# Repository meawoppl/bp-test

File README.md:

# PCB workspace

Choose a board in the portal using the selector configured in [`.kicad-pcb.json`](.kicad-pcb.json).

**Moved out (2026-10-20):**

- The ESP32 + iCE40 "gumstick" module (v1 DF40 module, v2 M.2 draft) and its
  programming carrier now live in **[OrbitalCommons/gumstick](https://github.com/OrbitalCommons/gumstick)**
  (public, history preserved; v1 ordered files under Git tag `v1`). Start with the
  [v1 ICD](https://github.com/OrbitalCommons/gumstick/blob/main/current-df40-connectors/docs/ICD-v1.md).
  It is included here as the submodule `third_party/gumstick`
  (`git submodule update --init`) because the Tesla controller scripts read the carrier.
- The GPS time calibrator, now named **StratumZero** (board, case, firmware,
  gateware, validation plan), lives in **[OrbitalCommons/stratumzero](https://github.com/OrbitalCommons/stratumzero)**
  (private for now).

Boards here:

- [Tesla coil controller](boards/tesla-coil-controller/README.md).
- [Original MainBoard](boards/mainboard-reference): native KiCad import for reference; original Fusion/Eagle exports in [source/fusion](source/fusion).
- Direction LED tester: existing board and fabrication files described below.

# Direction LED Differential Input Test Board

A compact 5 V BNC polarity indicator and Backplane workflow test project.

## Revision C

The schematic, 32 × 20 mm PCB, and fabrication files now match. The board is
73% smaller than the original 75 × 32 mm layout. The BNC body sits at the
left edge with its barrel overhanging, and the two indicators sit together on
the right. All routing is on top copper, with no vias.

- D1 / `+` (green 1206) lights when the BNC center is positive relative to its shell.
- D2 / `-` (red 1206) lights when the center is negative relative to its shell.
- A shared 1 kOhm 0805 resistor feeds directly antiparallel LEDs, limiting current
  and allowing the conducting LED to limit reverse voltage across the other.

There are four components: J1, R1, D1, and D2. R2 is removed.

[Layout drawing](docs/layout-review.svg) · [3D view](docs/layout-3d.png) ·
[Schematic](docs/schematic-review.svg)

## Verification and ordering

KiCad 10.0.6 ERC: **0 violations**. DRC with schematic parity: **0 violations,
0 unconnected items, 0 parity issues**, under the current project settings.
Gerbers, drills, BOM, and placements have been regenerated for revision C.

The package is ready for fabrication/assembly review, not an already approved
order. Confirm JLCPCB stock, through-hole assembly of J1, and LED rotation in
the assembly preview. No physical prototype has been tested. See the
[manufacturing notes](docs/manufacturing-notes.md) and [fabrication package](fab/README.md).

## Project files

| File or directory | Purpose |
| --- | --- |
| `direction-led-tester.kicad_pro` | KiCad project settings |
| `direction-led-tester.kicad_sch` | Revision C schematic |
| `direction-led-tester.kicad_pcb` | Revision C, 32 × 20 mm board |
| `bp-test.kicad_sym` | Vendored KiCad resistor and LED symbols |
| `fp-lib-table`, `sym-lib-table` | Project-local library mappings |
| `Resistor_SMD.pretty/`, `LED_SMD.pretty/` | Local KiCad footprints |
| `3dmodels/` | Resistor and LED STEP models |
| `lcsc/` | BNC symbol, corrected footprint, and STEP/WRL source models |
| `fab/` | Revision C fabrication, assembly, and check outputs |

The [workflow log](docs/plugin-workflow-log.md) records plugin testing and prior
revisions; use the current manufacturing notes for ordering requirements.

## Tesla coil controller

[Acquisition-first controller development](boards/tesla-coil-controller/README.md): eight simultaneous ADC channels, module v1 carrier interface, and two routed UD2.7-derived GDT bridges. This is an unfinished development board, not a fabrication release.

## License

[MIT](LICENSE). Third-party datasheets, vendor 3D models and imported library
files included for reference keep their own terms; see
`NOTICE`.

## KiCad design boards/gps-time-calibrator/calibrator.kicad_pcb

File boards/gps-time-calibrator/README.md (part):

# GPS optical time calibrator carrier — revision A, routed prototype

180 × 100 mm carrier for the **ordered module v1**, using the programming carrier's exact mating contacts and pad numbering. The ordered daughterboard and programmer files are unchanged. Connector-first routing is complete with clean native ERC, DRC and schematic parity. See `docs/routing-review.md` and `fab/STATUS.md` for validation scope and prototype bring-up checks.

## Optical display

Four identical rows of sixteen green 1206 LEDs (YLED1206G / C30584801) show bit 15 at the left through bit 0 at the right. Rows update together, without multiplexing. Each LED has its own **470 Ω, 1%, 0805** resistor. Sixteen AO3400A MOSFETs switch the columns through two SN74LVC541 buffers, with individual gate resistors and pulldowns. Every LED has its own 100 nF bypass beside its resistor (64 identical placements, so all LEDs see the same local supply at turn-on), and each column adds a 10 µF reservoir. All discrete resistors, capacitors and inductors are 0805 or larger; exact substitutions are in `docs/passive-parts-0805.json`.

Expected display current is approximately 0.26–0.33 A with all LEDs on, depending on LED forward voltage. Equal resistors reduce electrical mismatch but do not remove optical bin variation; use a common LED lot and measure brightness, supply bounce and optical edge timing on assembled hardware.

## USB power and installation

J3 is USB-C power and native USB data. The daughterboard and local logic are always powered from VBUS. The ESP32 reads HUSB238 source/contract status over I²C, enables the TPS259531 switched 5 V domain, and independently controls GPS and OCXO regulator enables. The NOR gate is removed. HUSB238 defaults to a 5 V / 3 A request; higher-voltage requests are forbidden because the always-on domain is fed directly from VBUS.

The eFuse has a nominal 2.48 A switched-load limit and approximately 12 ms ramp. Its current mirror is filtered to ESP GPIO3 / ADC1_CH2. Always-on current bypasses this measurement. Firmware must enforce the source's total budget, sequence the rails, and prevent UART back-powering; this firmware is not implemented here. See [power control, pin mapping and thermal calculations](docs/power-control.md).

There are no BOOT/RUN or RESET switches: the installed module stays in normal run mode using its own strap and EN pullups. Its existing firmware/ROM USB behavior must support the intended recovery procedure; this carrier does not provide a hardware boot override.

The module body extends from x=145 to 165 mm and y=10 to 55 mm, flush with the carrier's top edge. J1/J2 are at (155,24.3) and (155,49.3) mm, retaining 25 mm spacing. H1 is at their midpoint (155,36.8). Retain the programmer's 2.0 mm mounting spacer and frozen connector numbering.

## Right-edge connectors and GNSS

Top to bottom: USB-C J3, input SMA J6, output SMA J7, GPS antenna SMA J5. The SMA connectors are Amphenol 132289 edge-launch parts with approximately 11.43 mm projection beyond the edge and a nominal 1.57 mm (.062-inch) board slot.

Input accepts 0–5 V logic into a TLV3501 comparator referenced to half the 5 V supply, nominally 2.5 V. A 3.3 V Schmitt buffer feeds FPGA, ESP32 and GNSS EXTINT. Output is an AHCT buffer producing 5 V logic into a **high-impedance receiver**, not 5 V into a 50 Ω termination. Neither port should be treated as a protected industrial-voltage input.

MAX-M10S provides UART to ESP GPIO43/44 and PPS to FPGA G0 / ESP GPIO38. Its RF pin 11 connects straight along the top layer to J5, following the original board's topology. The receiver was moved left to accommodate the larger 0805 bias choke and capacitor. The module's VCC_RF output feeds the antenna through 10 Ω and 27 nH; confirm antenna current (50 mA maximum), voltage drop and RF performance. The separate antenna power switch is removed. RESET_N connects to ESP32 GPIO40 through 33 Ω. Backup power follows the receiver supply; there is no battery.

## Precision oscillator

Y1 is the manually assembled **Abracon AOC97FAJC-10.0000**, 10 MHz, 3.3 V OCXO. It has a dedicated TPS7A4533 1.5 A linear supply, enabled by GPIO5, local bypassing, and a 33 Ω series clock resistor to J2 pin 32 / FPGA IOB_3B_G6. Allow the specified warmup before precision measurements. This is a concrete replacement for the original project's unpopulated, untested oscillator provision; firmware must be adapted to 10 MHz.

Y1 is separately procured and excluded from the JLCPCB placement/BOM pair. Its local 3D model is an illustrative dimensional envelope, not manufacturer CAD.

## Stackup and release checks

Nominal 1.6 mm, four-layer JLC04161H-7628 construction is intended for the SMA slots. Outer copper 0.035 mm; outer dielectric 0.21040 mm; inner copper 0.0152 mm; core dielectric 1.065 mm. Source: https://jlcpcb.com/impedance . The nominal RF feed remains 0.26 mm wide with a 0.15 mm coplanar-ground clearance target. The manufacturer coated-coplanar calculation gives 50.50 ohm nominal; see `docs/rf/GPS-FEED.md`. Confirm the finished stackup, launch and bias tee at fabrication/bring-up. USB data is routed as a nearby pair for the module's full-speed interface.

The intended optical word is in 1/65536-second units (15.258789 µs per LSB). Sub-LSB calibration uses rolling-shutter transitions; the hardware alone does not establish absolute microsecond accuracy. Existing firmware is incomplete. `docs/display-map.json` and `docs/circuit.json` define the current mapping and circuit.

Canonical KiCad files are authoritative. Initial construction scripts are destructive and must not be rerun over incremental layout work. Generated fabrication and assembly outputs correspond to the routed PCB. Assembly orientation approval, power/thermal measurements and RF/optical timing validation remain prototype release checks.

## Schematic presentation

The complete circuit is on one A1 sheet, with dashed functional sections matching the module schematic. Filters, regulator support parts, bias networks and decouplers are connected by wires and conventional supply/ground symbols. The optical display is grouped into four banks of four columns, each showing its four individual resistor/LED branches, MOSFET and bypass pair. The single-page PDF is `docs/calibrator-schematic.pdf`. Regenerate with `tools/hardware/calibrator_schematic.py`; the generator preserves the audited circuit contract and changes PCB schematic paths only.

### Trigger input filter

C75 is 1 nF C0G, 50 V, 2%, 0805 (CCTC TCC0805COG102G500BT,
JLCPCB C5375915), shunting TRIGGER_LIMIT to GND after R8 (1 kohm).
It sits beside U9 IN+, with its ground pad thermally connected to the ground pour.
With R9 = 100 kohm, ideal low-impedance 0–5 V drive and a 2.5 V threshold,
tau is 0.990 us, cutoff is about 161 kHz, and nominal rising/falling threshold
latencies are 0.696/0.676 us (before comparator/translator delay).
These are calculated RC delays, not measured calibration constants. Source impedance,
amplitude, edge slew and component tolerances change them; short pulses can be rejected.
Account for the complete input path when validating absolute trigger timing.

### Date/time OLED

[Display assembly instructions (PDF)](docs/display-mounting.pdf) · [Editable instructions](docs/display-mounting.md)

DS1 is the HS HS96L03W2C03 (LCSC C5248080), a white 0.96-inch 128x64
SSD1315 I2C OLED module. It is manually installed below the daughterboard/OCXO,
with its four-pin edge toward the top of the carrier. Pin order is GND, 3.3V,
SCL, SDA; the default 7-bit I2C address is 0x3C. ESP_GPIO2 (J1.14) is SCL and
ESP_GPIO1 (J1.13) is SDA. These module pins were previously unused on this carrier.
R174/R175 are 4.7k pull-ups to +3V3_LOGIC. C76/C77 provide 100nF/10uF locally.
All support passives are 0805. Do not supply this module or its bus with 5V.

The footprint uses the manufacturer's 27.30 x 27.80 mm outline, a centered
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
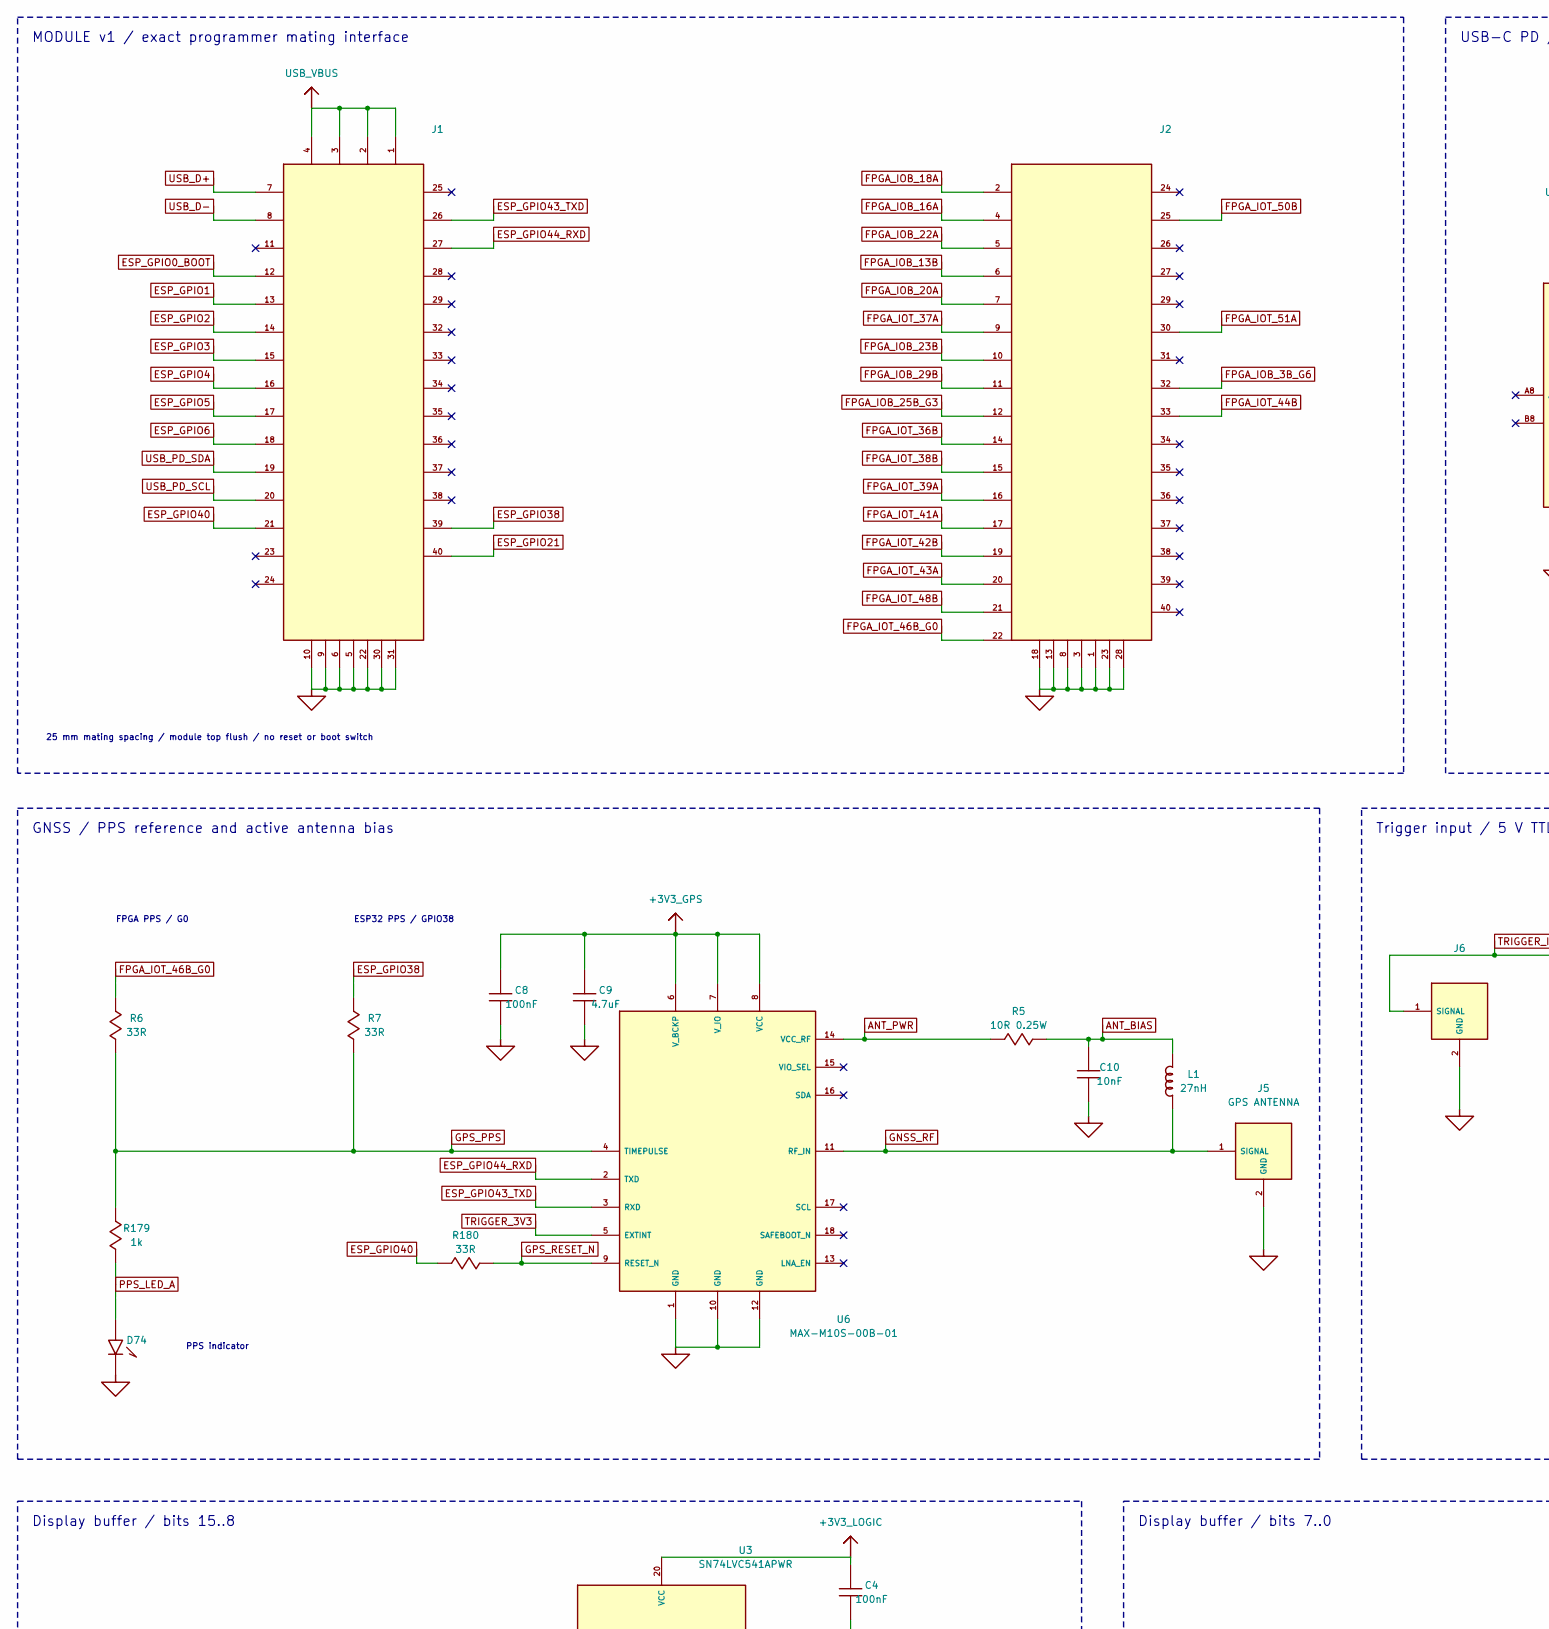
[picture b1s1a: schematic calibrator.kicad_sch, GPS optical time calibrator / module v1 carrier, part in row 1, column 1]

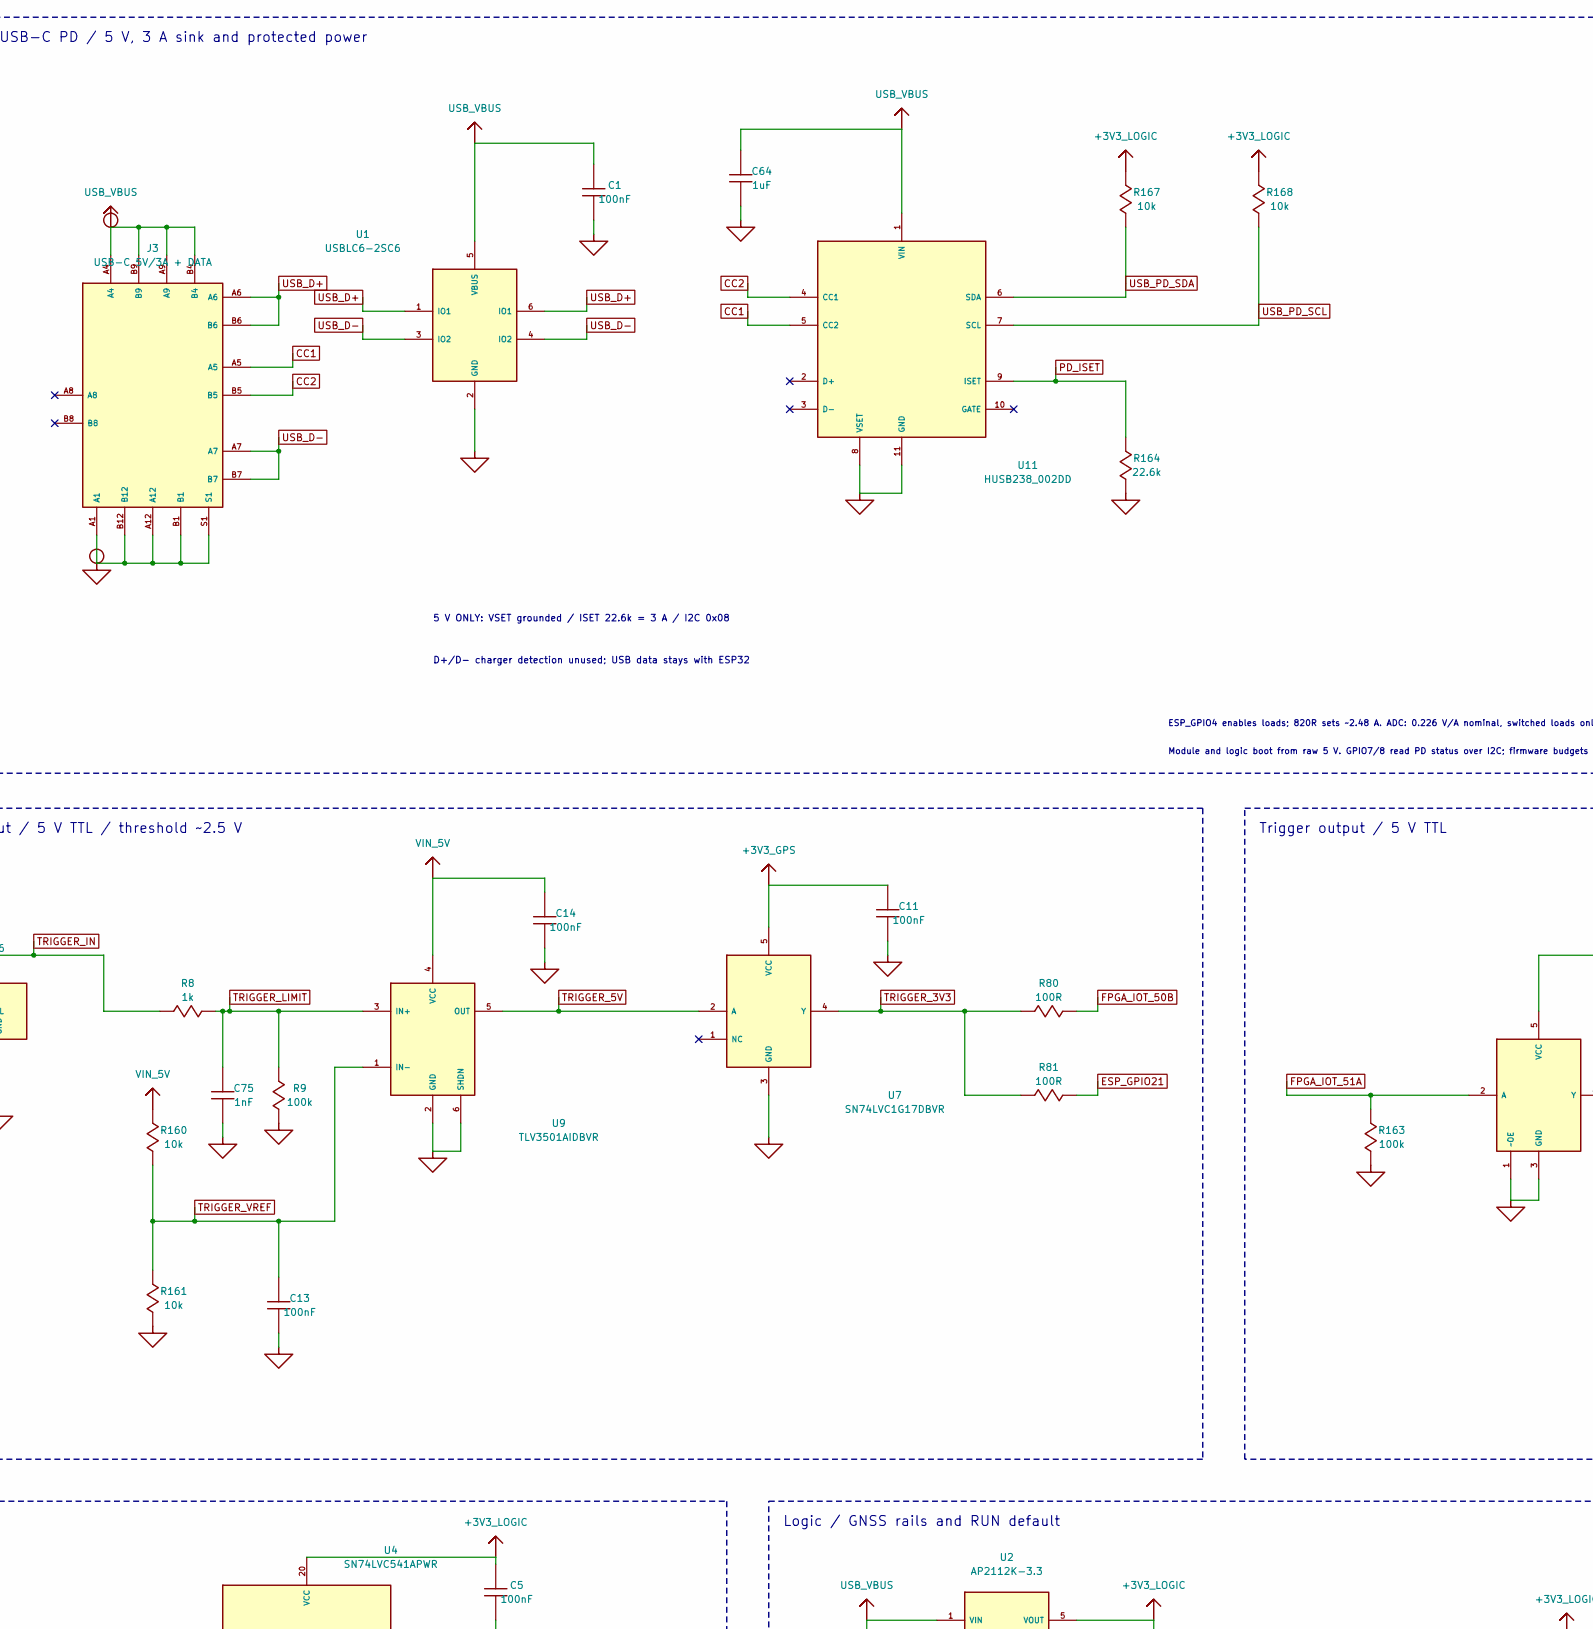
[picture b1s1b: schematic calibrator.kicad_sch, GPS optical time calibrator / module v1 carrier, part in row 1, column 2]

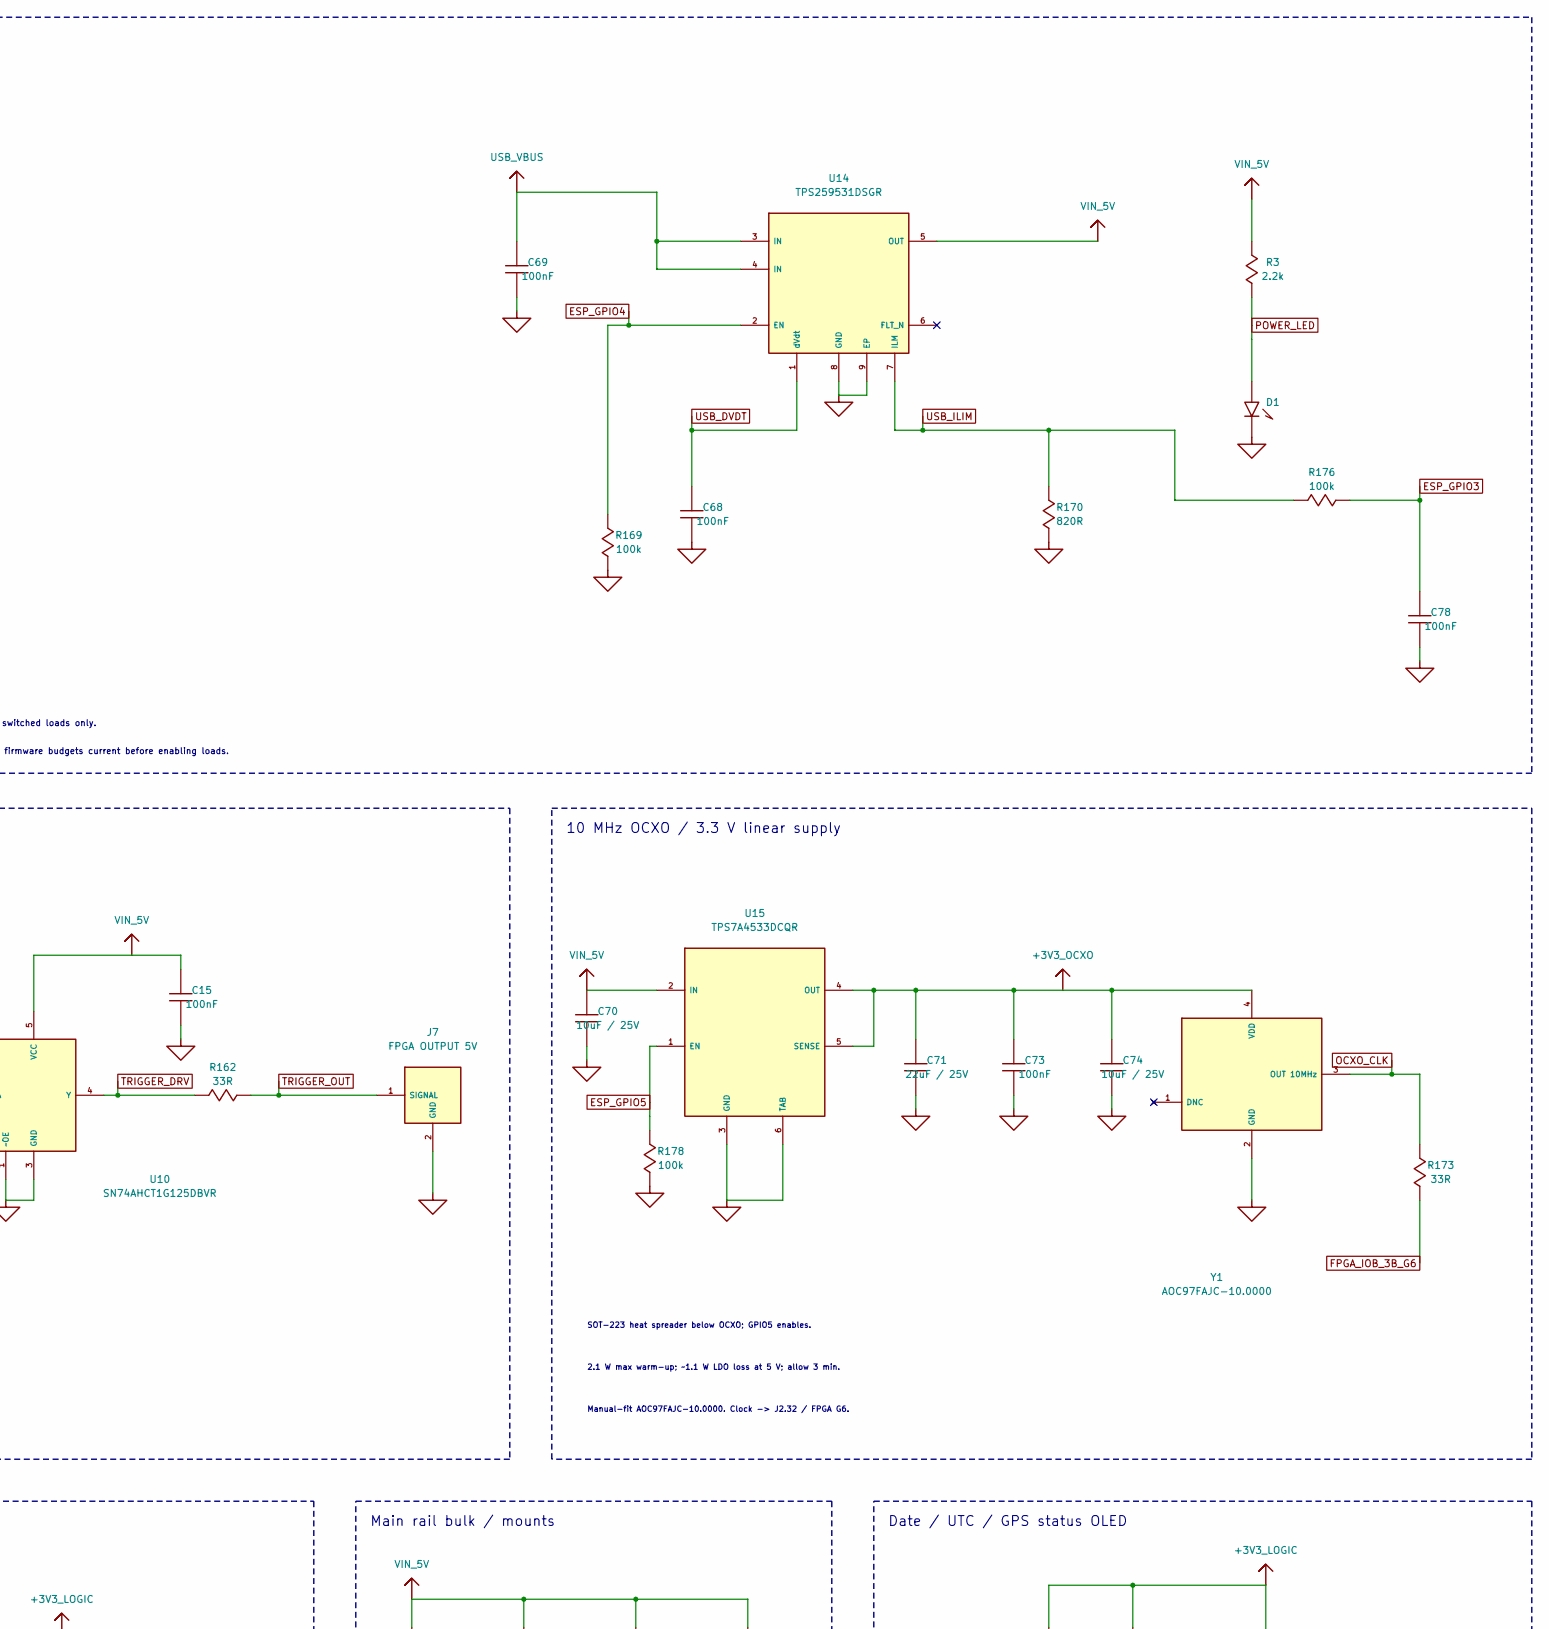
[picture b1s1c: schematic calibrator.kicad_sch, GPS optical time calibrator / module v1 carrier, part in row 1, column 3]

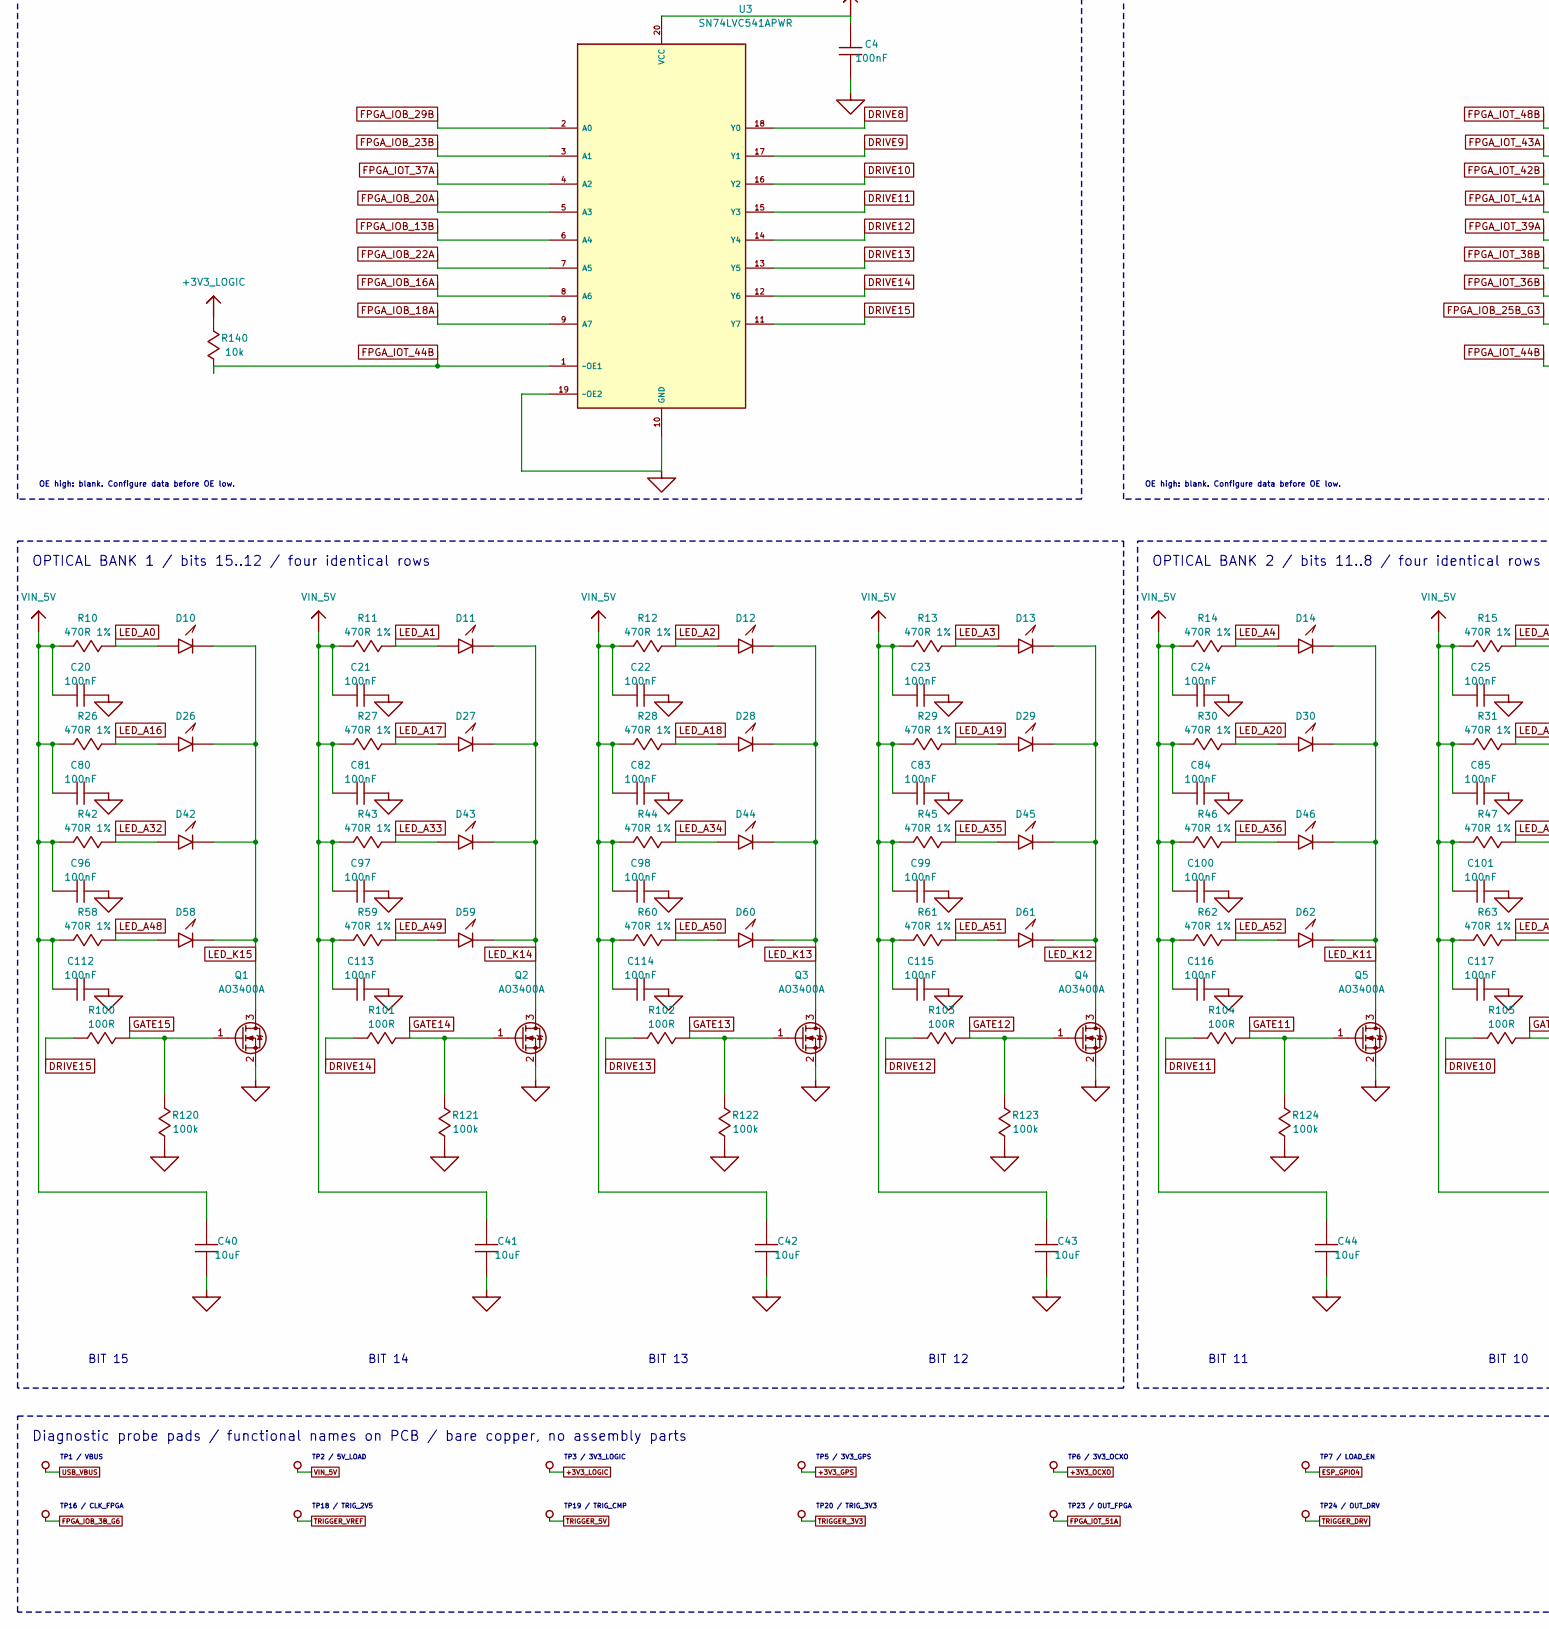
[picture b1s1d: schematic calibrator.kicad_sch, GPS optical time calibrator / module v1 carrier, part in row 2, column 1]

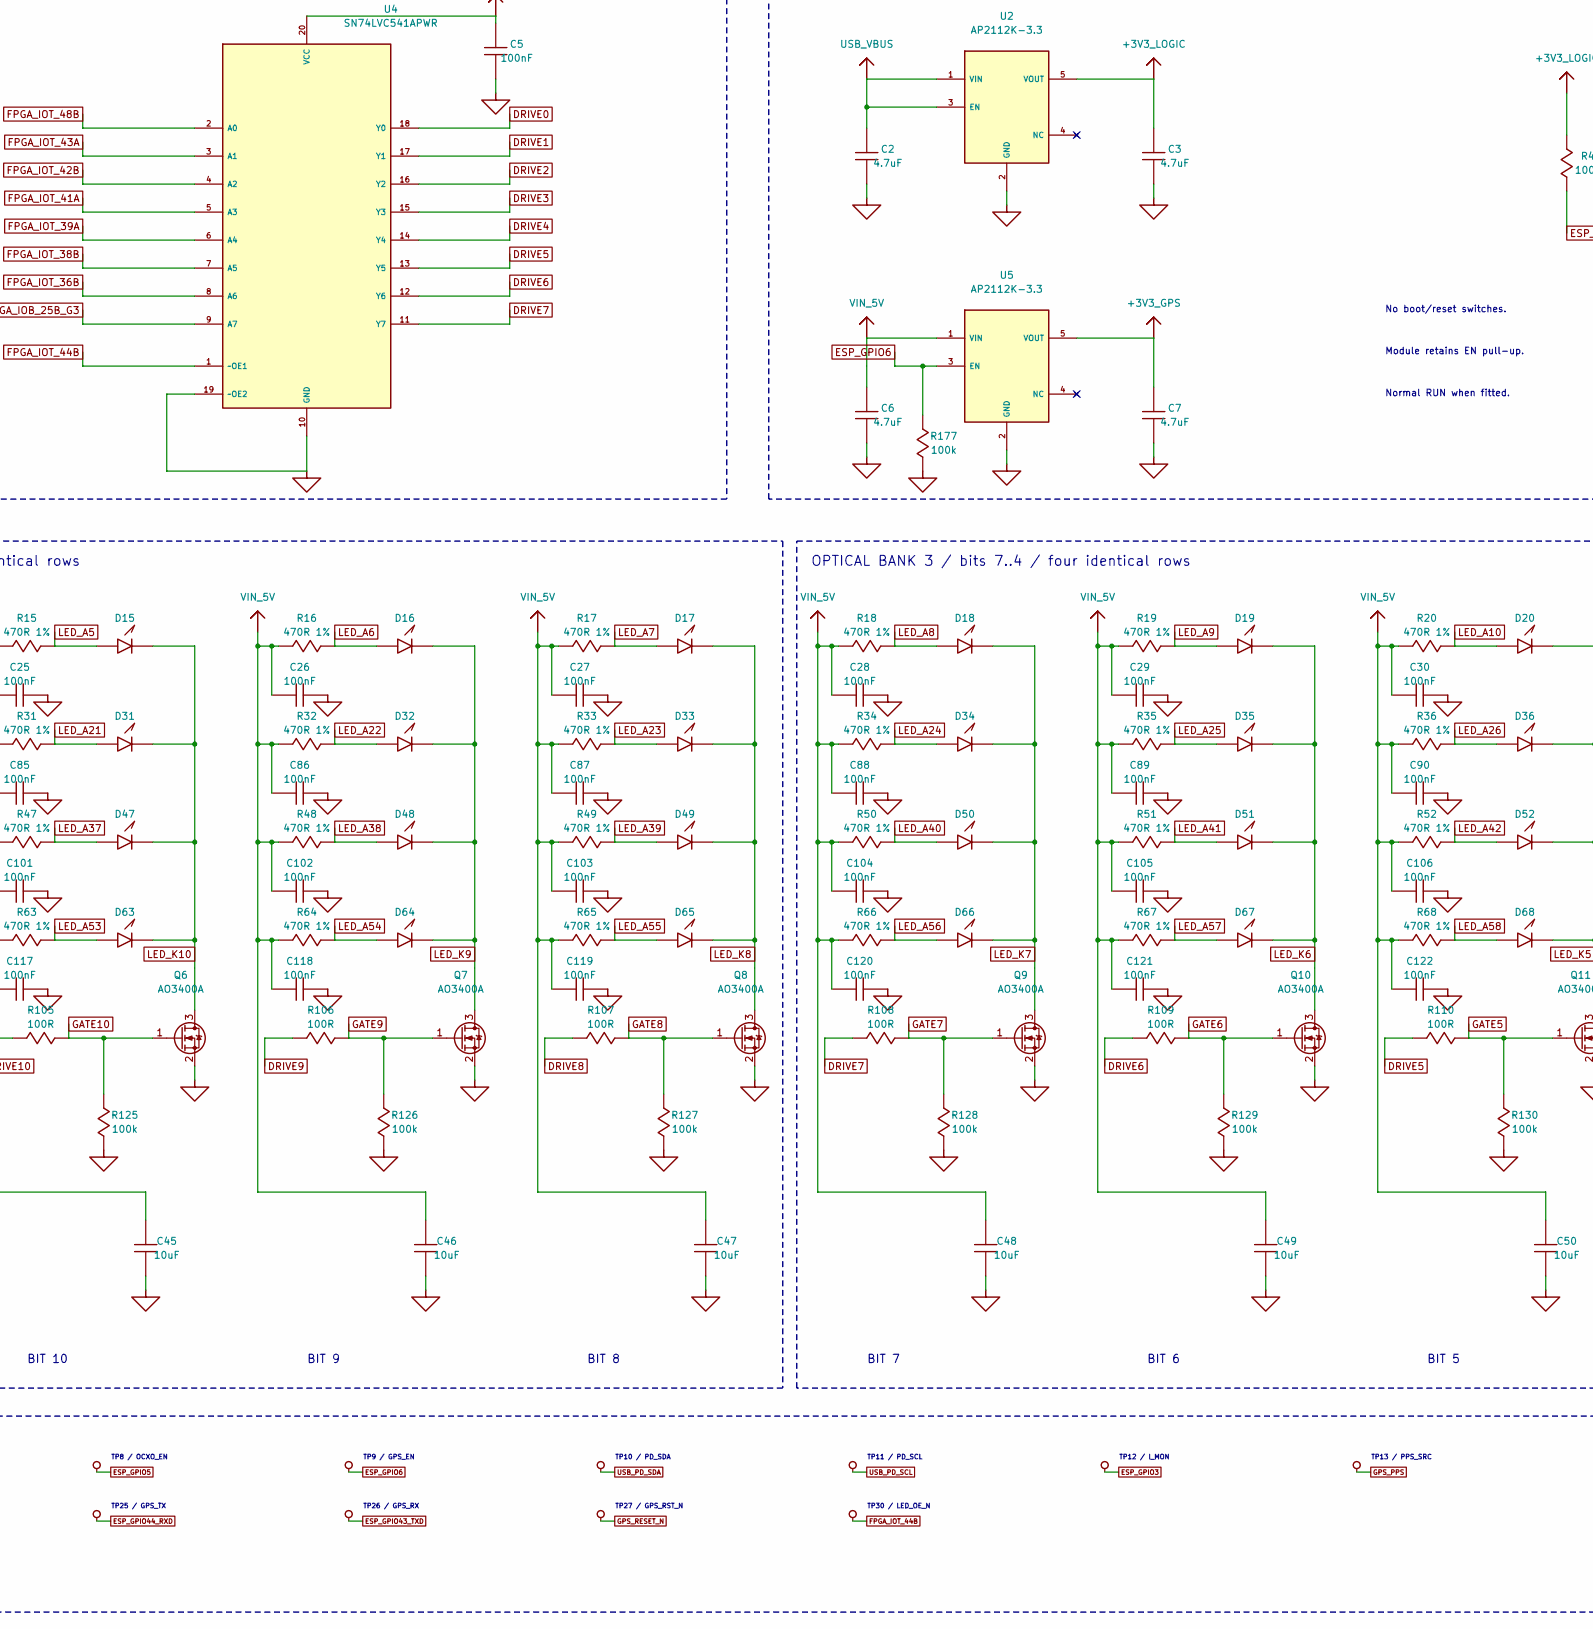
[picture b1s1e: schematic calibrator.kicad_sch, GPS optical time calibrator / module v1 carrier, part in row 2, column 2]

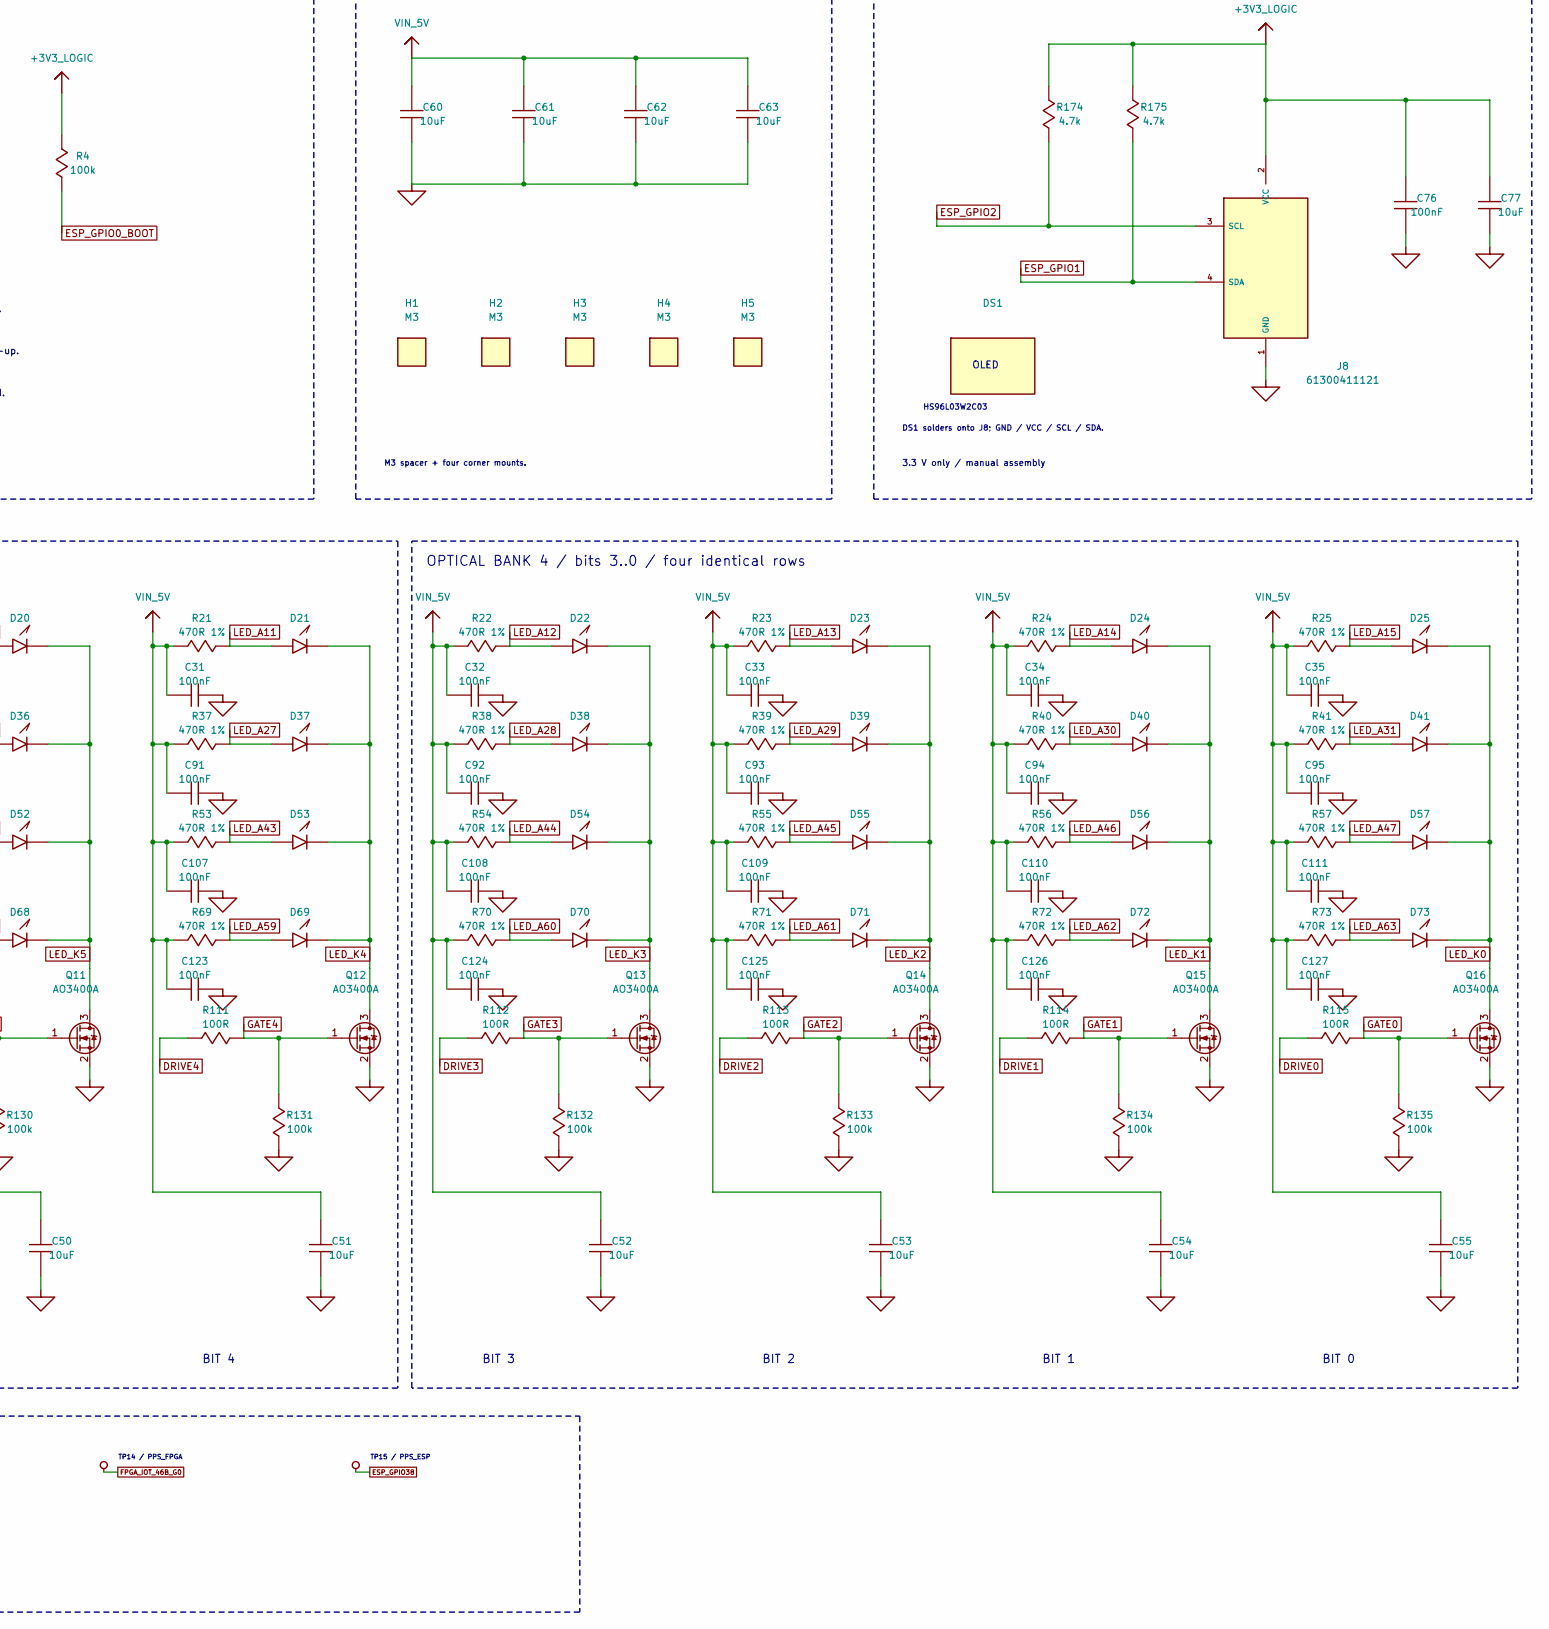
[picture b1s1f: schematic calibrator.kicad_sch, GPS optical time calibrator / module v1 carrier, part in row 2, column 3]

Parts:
C1, C4, C5, C8, C11, C13, C14, C15, C20, C21, C22, C23, C24, C25, C26, C27, C28, C29, C30, C31, C32, C33, C34, C35, C68, C69, C73, C76, C78, C80, C81, C82, C83, C84, C85, C86, C87, C88, C89, C90, C91, C92, C93, C94, C95, C96, C97, C98, C99, C100, C101, C102, C103, C104, C105, C106, C107, C108, C109, C110, C111, C112, C113, C114, C115, C116, C117, C118, C119, C120, C121, C122, C123, C124, C125, C126, C127: 100nF; C_0805_2012Metric; MPN CL21B104KBCNNNC; LCSC C1711
C2, C3, C6, C7, C9: 4.7uF; C_0805_2012Metric; MPN CL21A475KAQNNNE; LCSC C1779
C10: 10nF; C_0805_2012Metric; MPN CL21B103KBANNNC; LCSC C1710
C40, C41, C42, C43, C44, C45, C46, C47, C48, C49, C50, C51, C52, C53, C54, C55, C60, C61, C62, C63, C77: 10uF; C_0805_2012Metric; MPN CL21A106KAYNNNE; LCSC C15850
C64: 1uF; C_0805_2012Metric; MPN CL21B105KBFNNNE; LCSC C28323
C70, C74: 10uF / 25V; C_0805_2012Metric; MPN CL21A106KAYNNNE; LCSC C15850
C71: 22uF / 25V; C_0805_2012Metric; MPN CL21A226MAQNNNE; LCSC C45783
C75: 1nF; C_0805_2012Metric; MPN 0805CG102J500NT; LCSC C29925
D1, D74: GREEN; LED_0603_1608Metric; MPN XL-1608SYGC-06; LCSC C965805
D10, D11, D12, D13, D14, D15, D16, D17, D18, D19, D20, D21, D22, D23, D24, D25, D26, D27, D28, D29, D30, D31, D32, D33, D34, D35, D36, D37, D38, D39, D40, D41, D42, D43, D44, D45, D46, D47, D48, D49, D50, D51, D52, D53, D54, D55, D56, D57, D58, D59, D60, D61, D62, D63, D64, D65, D66, D67, D68, D69, D70, D71, D72, D73: GREEN; LED_1206_3216Metric; MPN YLED1206G; LCSC C30584801
DS1: HS96L03W2C03; HS96L03W2C03_27.3x27.8mm; MPN HS96L03W2C03; LCSC C5248080
H1, H2, H3, H4, H5: M3; MountingHole_3.2mm_M3; MPN M3
J1: DF40C-40DP-0.4V(51); J1_Module_v1_Mate; MPN DF40C-40DP-0.4V(51); LCSC C424643
J2: DF40C(2.0)-40DS-0.4V(51); J2_Module_v1_Mate; MPN DF40C(2.0)-40DS-0.4V(51); LCSC C597934
J3: USB-C 5V/3A + DATA; USB_C_Receptacle_HRO_TYPE-C-31-M-12; MPN TYPE-C-31-M-12; LCSC C165948
J5: GPS ANTENNA; SMA_Amphenol_132289_EdgeMount; MPN 132289; LCSC C3172723
J6: INPUT 5V / 2.5V THRESHOLD; SMA_Amphenol_132289_EdgeMount; MPN 132289; LCSC C3172723
J7: FPGA OUTPUT 5V; SMA_Amphenol_132289_EdgeMount; MPN 132289; LCSC C3172723
J8: 61300411121; OLED_Header_1x04_P2.54mm; MPN 61300411121; LCSC C5184785
L1: 27nH; L_Coilcraft_0805CS; MPN 0805CS-270XGLC; LCSC C38841159
Q1, Q2, Q3, Q4, Q5, Q6, Q7, Q8, Q9, Q10, Q11, Q12, Q13, Q14, Q15, Q16: AO3400A; SOT-23; MPN AO3400A; LCSC C20917
R3: 2.2k; R_0805_2012Metric; MPN 0805W8F2201T5E; LCSC C17520
R4, R9, R120, R121, R122, R123, R124, R125, R126, R127, R128, R129, R130, R131, R132, R133, R134, R135, R163, R169, R176, R177, R178: 100k; R_0805_2012Metric; MPN RC0805FR-07100KL; LCSC C96346
R5: 10R 0.25W; R_1206_3216Metric; MPN 1206W4F100JT5E; LCSC C17903
R6, R7, R162, R173, R180: 33R; R_0805_2012Metric; MPN 0805W8F330JT5E; LCSC C17634
R8, R179: 1k; R_0805_2012Metric; MPN 0805W8F1001T5E; LCSC C17513
R10, R11, R12, R13, R14, R15, R16, R17, R18, R19, R20, R21, R22, R23, R24, R25, R26, R27, R28, R29, R30, R31, R32, R33, R34, R35, R36, R37, R38, R39, R40, R41, R42, R43, R44, R45, R46, R47, R48, R49, R50, R51, R52, R53, R54, R55, R56, R57, R58, R59, R60, R61, R62, R63, R64, R65, R66, R67, R68, R69, R70, R71, R72, R73: 470R 1%; R_0805_2012Metric; MPN 0805W8F4700T5E; LCSC C17710
R80, R81, R100, R101, R102, R103, R104, R105, R106, R107, R108, R109, R110, R111, R112, R113, R114, R115: 100R; R_0805_2012Metric; MPN RC0805FR-07100RL; LCSC C105577
R140, R160, R161, R167, R168: 10k; R_0805_2012Metric; MPN 0805W8F1002T5E; LCSC C17414
R164: 22.6k; R_0805_2012Metric; MPN SCR0805F22K6; LCSC C3016901
R170: 820R; R_0805_2012Metric; MPN 0805W8F8200T5E; LCSC C17837
R174, R175: 4.7k; R_0805_2012Metric; MPN 0805W8F4701T5E; LCSC C17673
TP1: VBUS; TP_1p0mm
TP2: 5V_LOAD; TP_1p0mm
TP3: 3V3_LOGIC; TP_1p0mm
TP5: 3V3_GPS; TP_1p0mm
TP6: 3V3_OCXO; TP_1p0mm
TP7: LOAD_EN; TP_1p0mm
TP8: OCXO_EN; TP_1p0mm
TP9: GPS_EN; TP_1p0mm
TP10: PD_SDA; TP_1p0mm
TP11: PD_SCL; TP_1p0mm
TP12: I_MON; TP_1p0mm
TP13: PPS_SRC; TP_1p0mm
TP14: PPS_FPGA; TP_1p0mm
TP15: PPS_ESP; TP_1p0mm
TP16: CLK_FPGA; TP_1p0mm
TP18: TRIG_2V5; TP_1p0mm
TP19: TRIG_CMP; TP_1p0mm
TP20: TRIG_3V3; TP_1p0mm
TP23: OUT_FPGA; TP_1p0mm
TP24: OUT_DRV; TP_1p0mm
TP25: GPS_TX; TP_1p0mm
TP26: GPS_RX; TP_1p0mm
TP27: GPS_RST_N; TP_1p0mm
TP30: LED_OE_N; TP_1p0mm
U1: USBLC6-2SC6; SOT-23-6_U1; MPN USBLC6-2SC6; LCSC C7519
U2, U5: AP2112K-3.3; SOT-23-5; MPN AP2112K-3.3TRG1; LCSC C51118
U3, U4: SN74LVC541APWR; TSSOP-20_4.4x6.5mm_P0.65mm; MPN SN74LVC541APWR; LCSC C113281
U6: MAX-M10S-00B-01; ublox_MAX; MPN MAX-M10S-00B-01; LCSC C24834155
U7: SN74LVC1G17DBVR; SOT-23-5; MPN SN74LVC1G17DBVR; LCSC C7836
U9: TLV3501AIDBVR; SOT-23-6_U9; MPN TLV3501AIDBVR; LCSC C193413
U10: SN74AHCT1G125DBVR; SOT-23-5_U10; MPN SN74AHCT1G125DBVR; LCSC C7484
U11: HUSB238_002DD; HUSB238_DFN10_3x3mm; MPN HUSB238_002DD; LCSC C7471904
U14: TPS259531DSGR; DFN-8-1EP_2x2mm_P0.5mm_EP0.9x1.6mm; MPN TPS259531DSGR; LCSC C2155674
U15: TPS7A4533DCQR; SOT-223-6; MPN TPS7A4533DCQR; LCSC C2877942
Y1: AOC97FAJC-10.0000; AOC97_9.7x7.5mm; MPN AOC97FAJC-10.0000

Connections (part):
+3V3_GPS: C7.1, C8.1, C9.1, C11.1, TP5.1, U5.5 (VOUT), U6.6 (V_BCKP), U6.7 (V_IO), U6.8 (VCC), U7.5 (VCC)
+3V3_LOGIC: C3.1, C4.1, C5.1, C76.1, C77.1, J8.2 (VCC), R4.2, R140.1, R167.1, R168.1, R174.1, R175.1, TP3.1, U2.5 (VOUT), U3.20 (VCC), U4.20 (VCC)
+3V3_OCXO: C71.1, C73.1, C74.1, TP6.1, U15.4 (OUT), U15.5 (SENSE), Y1.4 (VDD)
ANT_BIAS: C10.1, L1.2, R5.2
ANT_PWR: R5.1, U6.14 (VCC_RF)
CC1: J3.A5, U11.5 (CC2)
CC2: J3.B5, U11.4 (CC1)
DRIVE0: R115.1, U4.18 (Y0)
DRIVE1: R114.1, U4.17 (Y1)
DRIVE2: R113.1, U4.16 (Y2)
DRIVE3: R112.1, U4.15 (Y3)
DRIVE4: R111.1, U4.14 (Y4)
DRIVE5: R110.1, U4.13 (Y5)
DRIVE6: R109.1, U4.12 (Y6)
DRIVE7: R108.1, U4.11 (Y7)
DRIVE8: R107.1, U3.18 (Y0)
DRIVE9: R106.1, U3.17 (Y1)
DRIVE10: R105.1, U3.16 (Y2)
DRIVE11: R104.1, U3.15 (Y3)
DRIVE12: R103.1, U3.14 (Y4)
DRIVE13: R102.1, U3.13 (Y5)
DRIVE14: R101.1, U3.12 (Y6)
DRIVE15: R100.1, U3.11 (Y7)
ESP_GPIO0_BOOT: J1.12, R4.1
ESP_GPIO1: J1.13, J8.4 (SDA), R175.2
ESP_GPIO2: J1.14, J8.3 (SCL), R174.2
ESP_GPIO3: C78.1, J1.15, R176.2, TP12.1
ESP_GPIO4: J1.16, R169.1, TP7.1, U14.2 (EN)
ESP_GPIO5: J1.17, R178.1, TP8.1, U15.1 (EN)
ESP_GPIO6: J1.18, R177.1, TP9.1, U5.3 (EN)
ESP_GPIO21: J1.40, R81.2
ESP_GPIO38: J1.39, R7.2, TP15.1
ESP_GPIO40: J1.21, R180.1
ESP_GPIO43_TXD: J1.26, TP26.1, U6.3 (RXD)
ESP_GPIO44_RXD: J1.27, TP25.1, U6.2 (TXD)
FPGA_IOB_3B_G6: J2.32, R173.2, TP16.1
FPGA_IOB_13B: J2.6, U3.6 (A4)
FPGA_IOB_16A: J2.4, U3.8 (A6)
FPGA_IOB_18A: J2.2, U3.9 (A7)
FPGA_IOB_20A: J2.7, U3.5 (A3)
FPGA_IOB_22A: J2.5, U3.7 (A5)
FPGA_IOB_23B: J2.10, U3.3 (A1)
FPGA_IOB_25B_G3: J2.12, U4.9 (A7)
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
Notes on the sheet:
MODULE v1 / exact programmer mating interface
25 mm mating spacing / module top flush / no reset or boot switch
USB-C PD / 5 V, 3 A sink and protected power
5 V ONLY: VSET grounded / ISET 22.6k = 3 A / I2C 0x08
D+/D- charger detection unused; USB data stays with ESP32
ESP_GPIO4 enables loads; 820R sets ~2.48 A. ADC: 0.226 V/A nominal, switched loads only.
Module and logic boot from raw 5 V. GPIO7/8 read PD status over I2C; firmware budgets current before enabling loads.
GNSS / PPS reference and active antenna bias
FPGA PPS / G0
ESP32 PPS / GPIO38
PPS indicator
Trigger input / 5 V TTL / threshold ~2.5 V
Trigger output / 5 V TTL
10 MHz OCXO / 3.3 V linear supply
SOT-223 heat spreader below OCXO; GPIO5 enables.
2.1 W max warm-up; ~1.1 W LDO loss at 5 V; allow 3 min.
Manual-fit AOC97FAJC-10.0000. Clock -> J2.32 / FPGA G6.
Display buffer / bits 15..8
OE high: blank. Configure data before OE low.
Display buffer / bits 7..0
Logic / GNSS rails and RUN default
No boot/reset switches.
Module retains EN pull-up.
Normal RUN when fitted.
Main rail bulk / mounts
M3 spacer + four corner mounts.
Date / UTC / GPS status OLED
OLED
HS96L03W2C03
DS1 solders onto J8; GND / VCC / SCL / SDA.
3.3 V only / manual assembly
OPTICAL BANK 1 / bits 15..12 / four identical rows
BIT 15
BIT 14
BIT 13
BIT 12
OPTICAL BANK 2 / bits 11..8 / four identical rows
BIT 11
BIT 10
BIT 9

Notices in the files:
parts and their libraries:
COPYRIGHT: Copyright (C) 2025 Ultra Librarian. All rights reserved.
